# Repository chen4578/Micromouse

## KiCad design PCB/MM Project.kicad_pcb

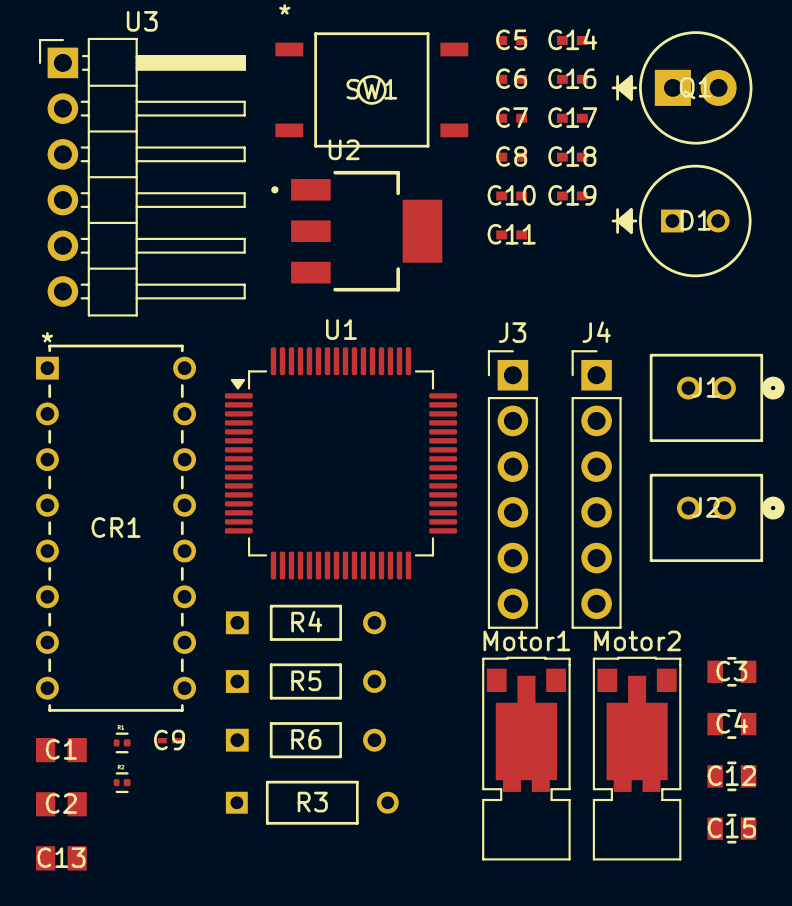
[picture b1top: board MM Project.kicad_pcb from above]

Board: 2 copper layers, 38 parts (0 on the bottom side), 22 nets, no tracks yet.

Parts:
C1, C2: 2.2 uF; CAP_CL_21_SAM
C3: 0.1 uF; G-21_MUR
C4, C12, C15: 10 uF; G-21_MUR
C5, C6, C7, C8, C10, C11, C19: 0.1 uF; CAP_CL05_SAM
C9: 1 uF; CAP_CL03_SAM
C13: 22 uF; CAP_CL_21_SAM
C14, C17: 4.7uF; CAP_CL05_SAM
C16: 0.1uF; CAP_CL05_SAM
C18: 4.7 uF; CAP_CL05_SAM
CR1: L293D; PowerDIP-16_STM
D1: IR Emitter; LED_INL-5AMIR15_INO
J1: JST 1; CONN2_B2B-PH-K-S_JST
J2: JST 2; CONN2_B2B-PH-K-S_JST
J3, J4: Conn_01x06_Pin; PinHeader_1x06_P2.54mm_Vertical
Motor1, Motor2: Vybronics_VZ30C1T8219732L
Q1: IR Reciver; SFH 313 FA-3&slash_4_OSR
R1, R2: 10 kOhm; RESC0603X26N
R3: 51 Ohm; RES_CMF50_VIS
R4: 100 Ohm; RES_MRS16_VIS
R5: 47 kOhm; RES_MRS16_VIS
R6: 1.8kOhm; RES_MRS16_VIS
SW1: Button; SW4_FSM4JSMA_TEC
U1: STM32F205RGTx; LQFP-64_10x10mm_P0.5mm
U2: Voltage Regulator; SOT230P700X185-4N
U3: MOSFET; PinHeader_1x06_P2.54mm_Horizontal

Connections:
3V3: C3.2, C4.2, C5.2, C6.2, C7.2, C8.2, C9.1, C10.1, C13.1, C18.1, C19.2, CR1.1 (CHIPENABLE1), CR1.9 (CHIPENABLE2), J3.4, J4.4, Q1.2, R3.2, U1.1 (VBAT), U1.13 (VDDA), U1.19 (VDD), U1.32 (VDD), U1.48 (VDD), U1.64 (VDD), U2.2 (OUTPUT), U2.4 (VOUT)
GND: C1.1, C2.1, C3.1, C4.1, C5.1, C6.1, C7.1, C8.1, C9.2, C10.2, C11.2, C12.2, C13.2, C16.1, C17.1, C18.2, C19.1, CR1.13 (GND), J2.2, J3.1, J4.1, R1.2, R2.1, R5.1, R6.2, SW1.4, U1.12 (VSSA), U1.18 (VSS), U1.63 (VSS), U2.1 (GND), U3.3 (S)
MGND: C14.2, C15.2
ML1: CR1.6 (OUTPUT2), J4.6
ML2: CR1.3 (OUTPUT1), J4.5
MR1: CR1.14 (OUTPUT4), J3.6
MR2: CR1.11 (OUTPUT3), J3.5
NRST: C11.1, SW1.1, U1.7 (NRST)
unnamed: D1.2, R3.1
unnamed: J1.2, J2.1
unnamed: Q1.1, R6.1
unnamed: R1.1, U1.60 (BOOT0)
unnamed: R2.2, U1.28 (PB2)
unnamed: C1.2, U1.31 (VCAP_1)
unnamed: C2.2, U1.47 (VCAP_2)
unnamed: D1.1, U3.2 (D)
unnamed: R4.2, R5.2, U3.1 (G)
PA0: CR1.10 (INPUT3), J3.3
PA1: CR1.15 (INPUT4), J3.2
PA8: CR1.2 (INPUT1), J4.3
PA9: CR1.7 (INPUT2), J4.2
VCC: C12.1, C14.1, C15.1, C16.2, C17.2, CR1.8 (VS), CR1.16 (VSS), J1.1, U2.3 (INPUT)

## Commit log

2025-10-02 Create Power Delivery Schematic
2025-10-02 Create temp
